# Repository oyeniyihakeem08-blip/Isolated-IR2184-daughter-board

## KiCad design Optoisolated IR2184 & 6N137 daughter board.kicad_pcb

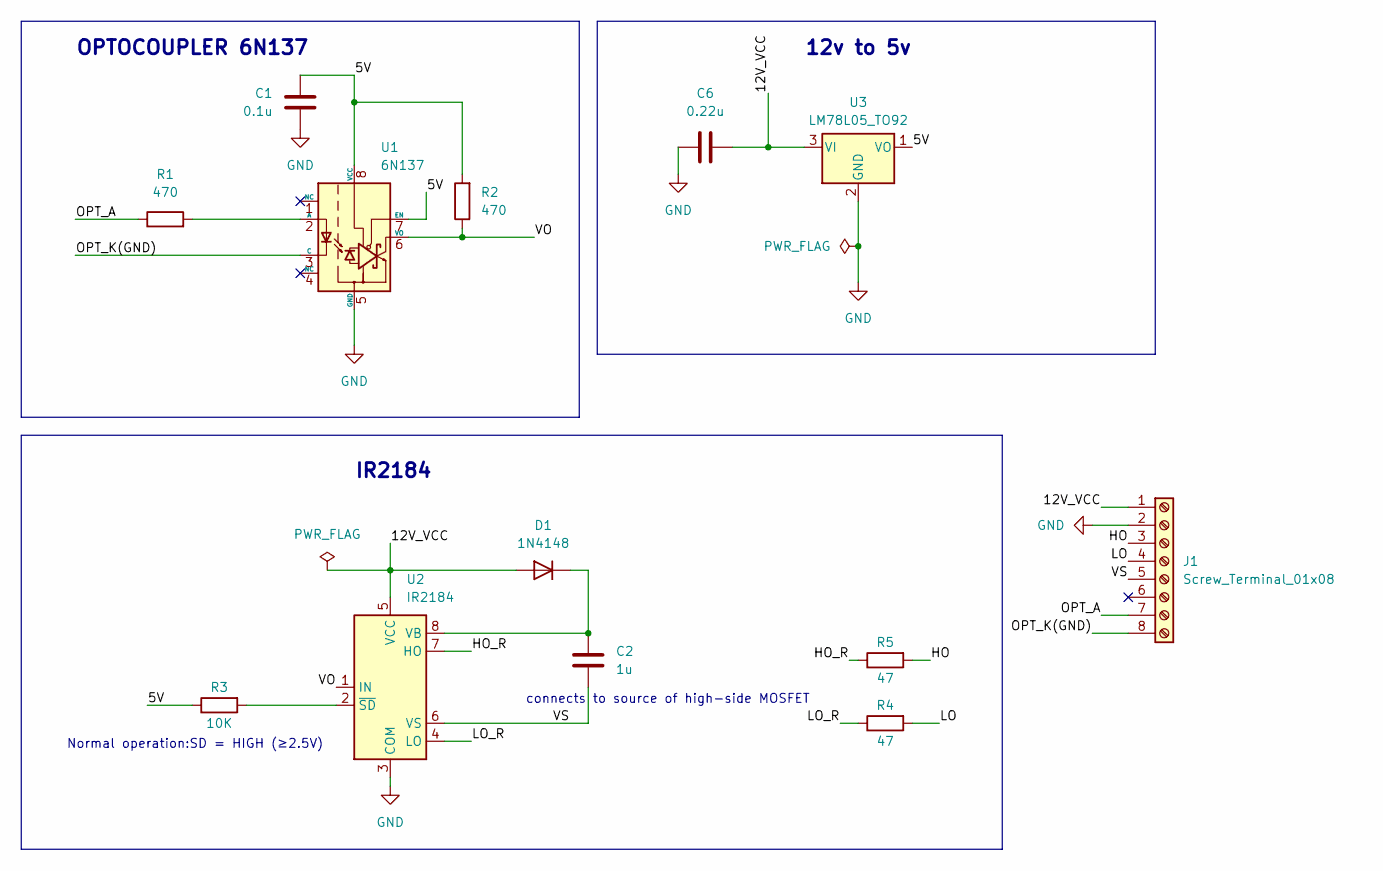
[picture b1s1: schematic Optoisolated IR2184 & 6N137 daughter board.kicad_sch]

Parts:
C1: 0.1u; C_Disc_D5.0mm_W2.5mm_P2.50mm; Voltage 50v; Manufacturer Part Number C326C104K5R5TA
C2: 1u; C_Disc_D5.0mm_W2.5mm_P2.50mm; Voltage 25v; Manufacturer Part Number RDEC71E105K0P1H03B
C6: 0.22u; C_Disc_D5.0mm_W2.5mm_P2.50mm; Voltage 50v; Manufacturer Part Number K224Z15Y5VF5TL2
D1: 1N4148; D_DO-35_SOD27_P7.62mm_Horizontal; Voltage .; Manufacturer Part Number 1N4148-TAP
J1: Screw_Terminal_01x08; TerminalBlock_Phoenix_PT-1,5-8-3.5-H_1x08_P3.50mm_Horizontal; Voltage .
R1, R2: 470; R_Axial_DIN0207_L6.3mm_D2.5mm_P7.62mm_Horizontal; Voltage .; Manufacturer Part Number CFR16J470R
R3: 10K; R_Axial_DIN0207_L6.3mm_D2.5mm_P7.62mm_Horizontal; Voltage .; Manufacturer Part Number CFR16J10K
R4, R5: 47; R_Axial_DIN0207_L6.3mm_D2.5mm_P7.62mm_Horizontal; Voltage .; Manufacturer Part Number LR0204F47R
U1: 6N137; DIP-8_W7.62mm; Voltage .; Manufacturer Part Number 6N137
U2: IR2184; DIP-8_W7.62mm; Voltage .; Manufacturer Part Number IR2184SPBF
U3: LM78L05_TO92; TO-220F-3_Vertical; Manufacturer Part Number LM7805CT/NOPB

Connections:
/5V: C1.1, R2.2, R3.1, U1.7 (EN), U1.8 (VCC), U3.1 (VO)
/12V_VCC: C6.2, D1.2 (A), J1.1, U2.5 (VCC), U3.3 (VI)
/HO: J1.3, R5.2
/HO_R: R5.1, U2.7 (HO)
/LO: J1.4, R4.2
/LO_R: R4.1, U2.4 (LO)
/OPT_A: J1.7, R1.1
/OPT_K(GND): J1.8, U1.3 (C)
/VO: R2.1, U1.6 (VO), U2.1 (IN)
/VS: C2.2, J1.5, U2.6 (VS)
GND: C1.2, C6.1, J1.2, U1.5 (GND), U2.3 (COM), U3.2 (GND)
unnamed: C2.1, D1.1 (K), U2.8 (VB)
unnamed: R1.2, U1.2 (A)
unnamed: R3.2, U2.2 (~SD)

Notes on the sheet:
Normal operation:SD = HIGH (≥2.5V)
IR2184
12v to 5v
OPTOCOUPLER 6N137
connects to source of high-side MOSFET

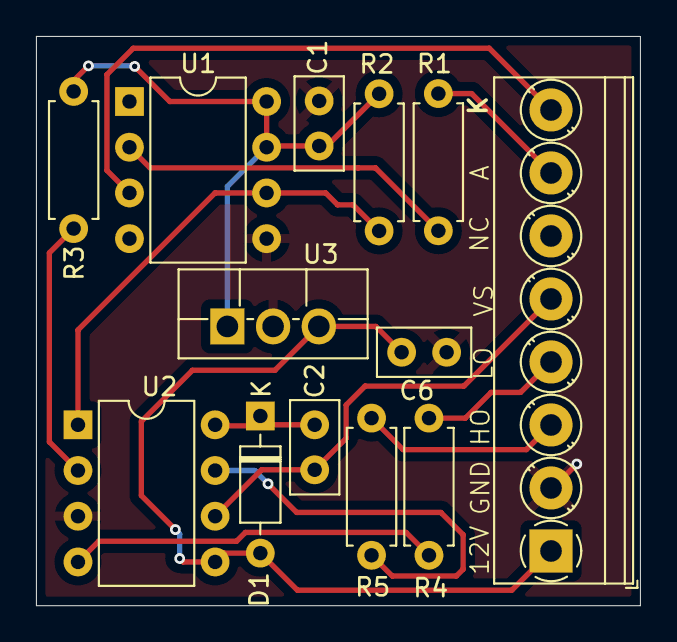
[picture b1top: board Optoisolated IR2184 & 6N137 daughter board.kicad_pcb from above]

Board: 2 copper layers, 33.6 x 31.6 mm, 13 parts (0 on the bottom side), 14 nets.

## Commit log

2025-12-12 uploaded schematics
2025-12-16 PCB LAYOUT
2025-12-16 Update project files
